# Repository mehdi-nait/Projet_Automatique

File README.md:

# Projet_Automatique

This project's aim is to provide a temperature control software, in order to maintain a copper plate under a specific, predefined temperature.

Used tools : AVR328P, LN298, HS25 Resistor and NTC Thermistor.

@ENSIM 2021

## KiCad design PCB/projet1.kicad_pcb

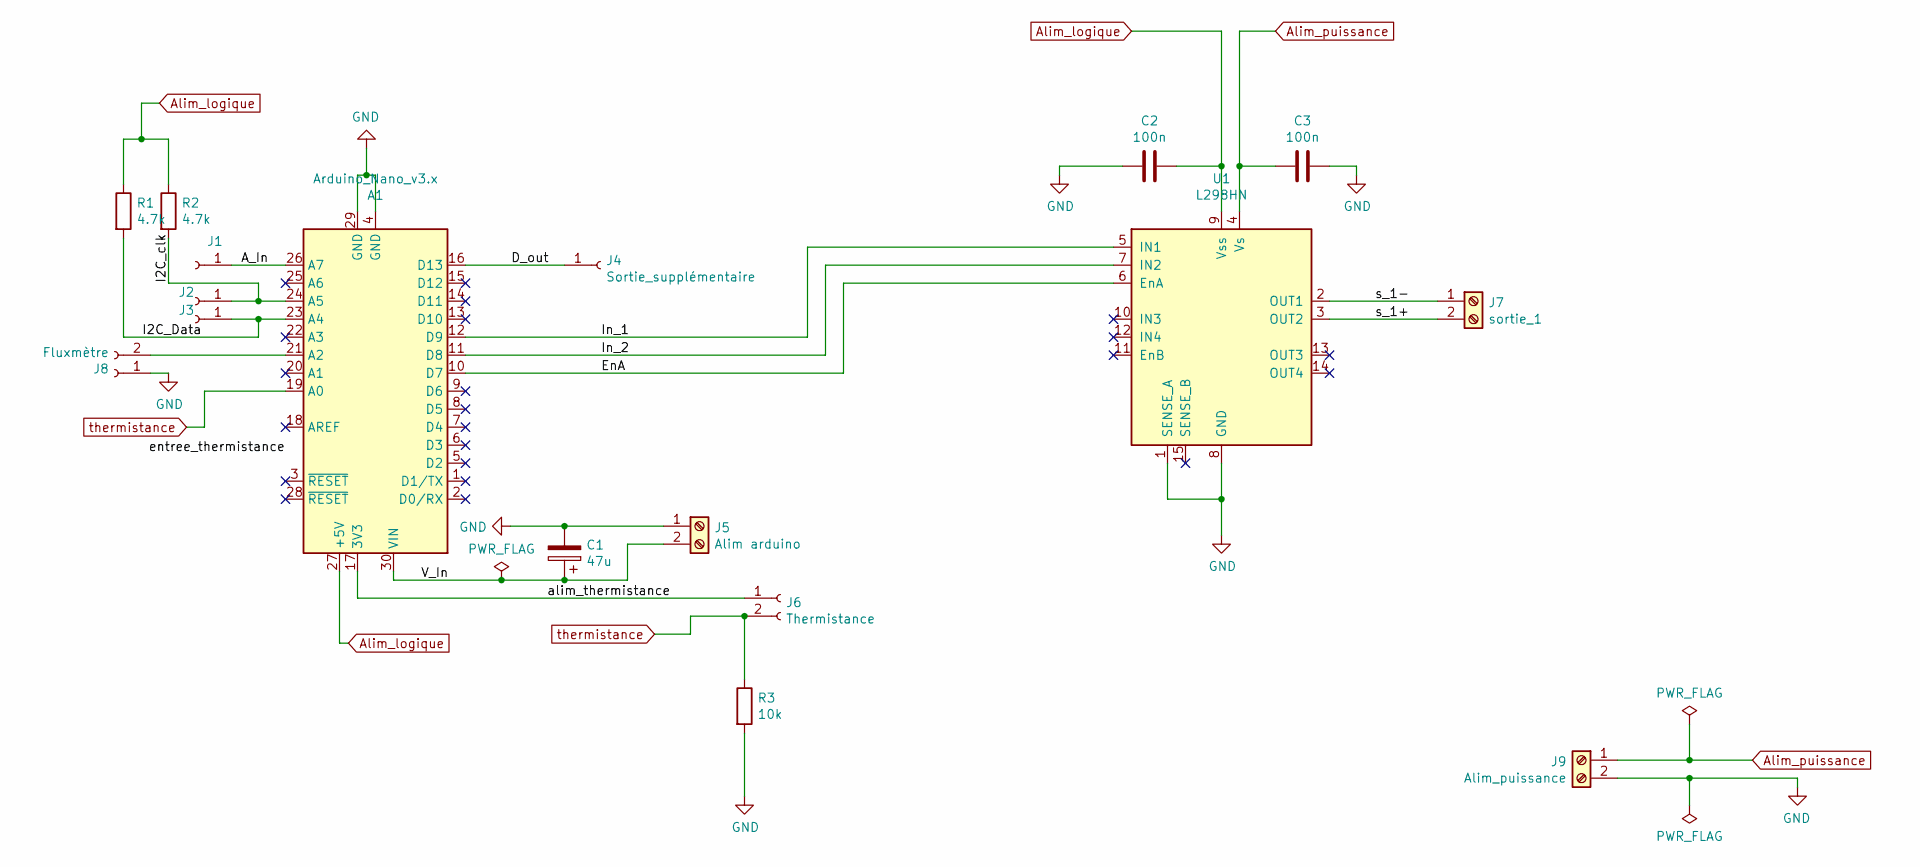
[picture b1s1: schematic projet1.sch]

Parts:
A1: Arduino_Nano_v3.x; Arduino_Nano
C1: 47u; CP_Radial_Tantal_D6.0mm_P5.00mm
C2, C3: 100n; CP_Radial_Tantal_D6.0mm_P5.00mm
J1: A_in_supplémentaire; PinSocket_1x01_P2.54mm_Vertical
J2: i2c_sda; PinSocket_1x01_P2.54mm_Vertical
J3: i2c_scl; PinSocket_1x01_P2.54mm_Vertical
J4: Sortie_supplémentaire; PinSocket_1x01_P2.54mm_Vertical
J5: Alim arduino; PinSocket_1x02_P2.54mm_Vertical
J6: Thermistance; PinSocket_1x02_P2.54mm_Vertical
J7: sortie_1; TerminalBlock_Phoenix_MPT-0,5-2-2.54_1x02_P2.54mm_Horizontal
J8: Fluxmètre; PinSocket_1x02_P2.54mm_Vertical
J9: Alim_puissance; TerminalBlock_Phoenix_MPT-0,5-2-2.54_1x02_P2.54mm_Horizontal
R1, R2: 4.7k; R_Axial_DIN0207_L6.3mm_D2.5mm_P10.16mm_Horizontal
R3: 10k; R_Axial_DIN0207_L6.3mm_D2.5mm_P10.16mm_Horizontal
U1: L298HN; TO-220-15_P2.54x2.54mm_StaggerOdd_Lead4.58mm_Vertical

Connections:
/A_In: A1.26 (A7), J1.1
/D_out: A1.16 (D13), J4.1
/EnA: A1.10 (D7), U1.6 (EnA)
/I2C_Data: A1.23 (A4), J3.1, R1.2
/I2C_clk: A1.24 (A5), J2.1, R2.2
/In_1: A1.12 (D9), U1.5 (IN1)
/In_2: A1.11 (D8), U1.7 (IN2)
/V_In: A1.30 (VIN), C1.1, J5.2
/alim_thermistance: A1.17 (3V3), J6.1
/s_1+: J7.2, U1.3 (OUT2)
/s_1-: J7.1, U1.2 (OUT1)
Alim_logique: A1.27 (+5V), C2.1, R1.1, R2.1, U1.9 (Vss)
Alim_puissance: C3.2, J9.1, U1.4 (Vs)
GND: A1.4 (GND), A1.29 (GND), C1.2, C2.2, C3.1, J5.1, J8.1, J9.2, R3.2, U1.1 (SENSE_A), U1.8 (GND)
unnamed: A1.21 (A2), J8.2
thermistance: A1.19 (A0), J6.2, R3.1

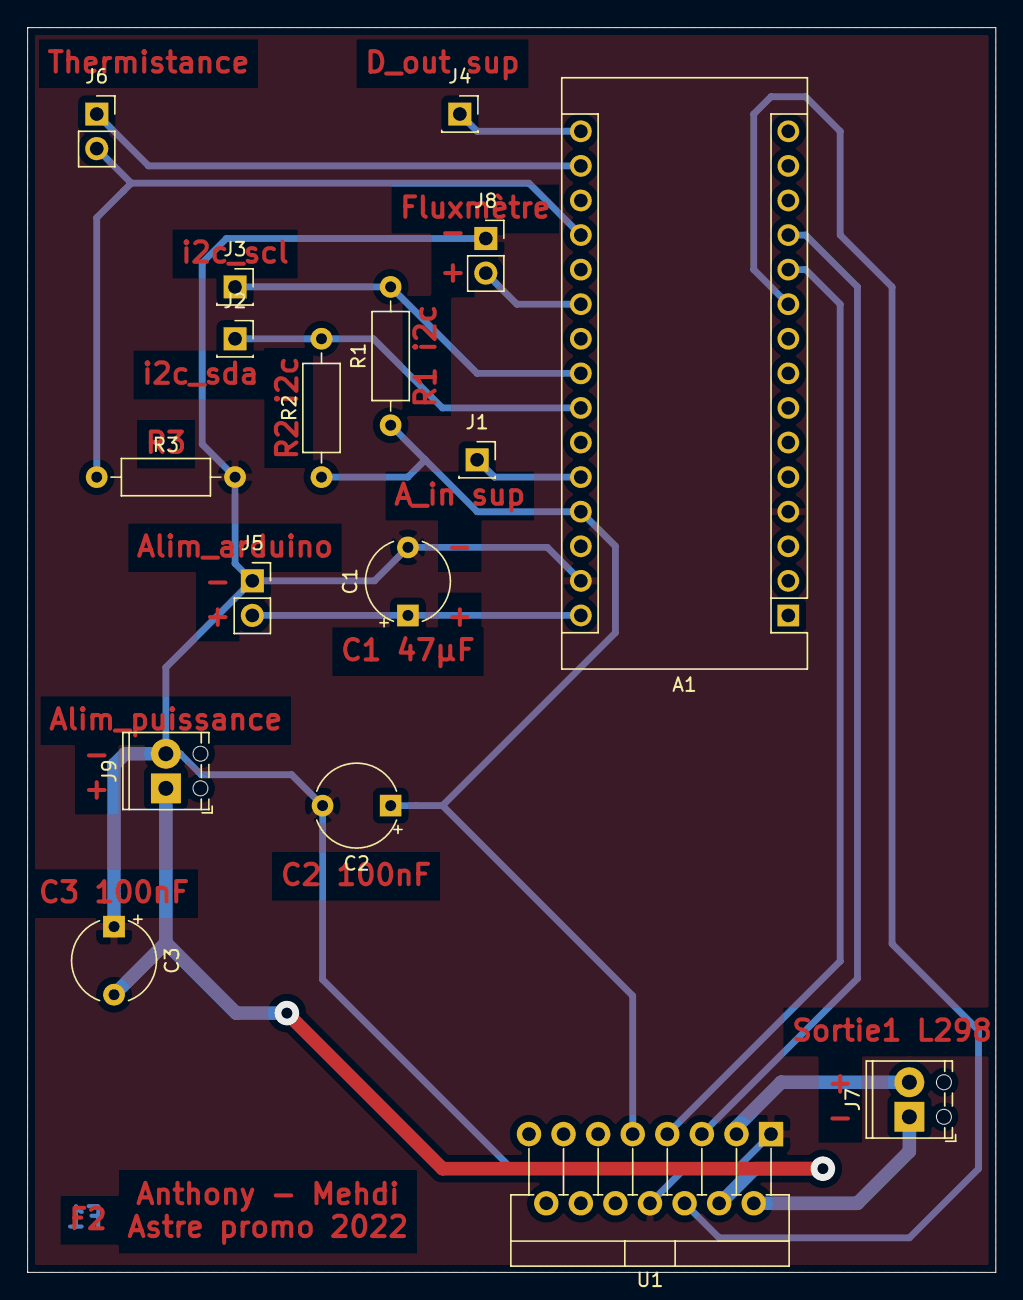
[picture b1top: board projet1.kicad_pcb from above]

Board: 2 copper layers, 71.1 x 91.4 mm, 17 parts (0 on the bottom side), 16 nets.

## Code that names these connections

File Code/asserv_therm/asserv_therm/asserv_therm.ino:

//Pin thermistance
int pin_therm = 5;

//Variable thermistance
int val;
double tension;
float temp;

int Consigne = 50;

//Pins L298N
int IN_1 = 13;  
int IN_2 = 12;
int EN_A = 10;

int debug = 0;

int Bdata = 10;
void setup() {
  // put your setup code here, to run once:
  //  Configuration du port de la thermistance en "entrée"
  pinMode(pin_therm,INPUT);
  
  //  Configuration des ports de la résistance chauffante en "sortie"
  pinMode(IN_1,OUTPUT);
  pinMode(IN_2,OUTPUT);
  pinMode(EN_A,OUTPUT);

  Serial.begin(9600);
  Serial.println("CLEARDATA"); 
  Serial.println("LABEL,temp,Bcolumn");
  Serial.println("RESETTIMER");
  
}

void loop() {
  // put your main code here, to run repeatedly:
  
  digitalWrite(IN_1,HIGH);
  digitalWrite(IN_2,LOW);

  val = analogRead(pin_therm);  // read the input pin
  tension = (val*3.3)/676;

  //3,8997x3 - 17,089x2 + 49,686x - 43,095
  temp = 3.8997*pow(tension,3) - 17.089*pow(tension,2)+ 49.686*tension - 43.095;

  //Serial.print(" Temperature :  ");
  //Serial.print(temp);

  
  
  Serial.println(temp);
  delay(1000);

}

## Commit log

2021-04-28 ajout des documents constructeur
2021-04-28 ajout du shéma pont H
2021-04-28 modification de la sortie
2021-04-28 adding comments
2021-05-12 ajout code thermistance + l298n et modif
2021-05-12 12.05.2021
2021-05-21 régulation de température ajoutée
2021-05-25 ajout de la réponse impulsionnelle
2021-05-25 amélioration de la courbe de réponse impulsionnelle et extraction des valeurs de la fonction de transfert
2021-05-26 ajout des captures pid tool
2021-06-01 ajout asservissement
